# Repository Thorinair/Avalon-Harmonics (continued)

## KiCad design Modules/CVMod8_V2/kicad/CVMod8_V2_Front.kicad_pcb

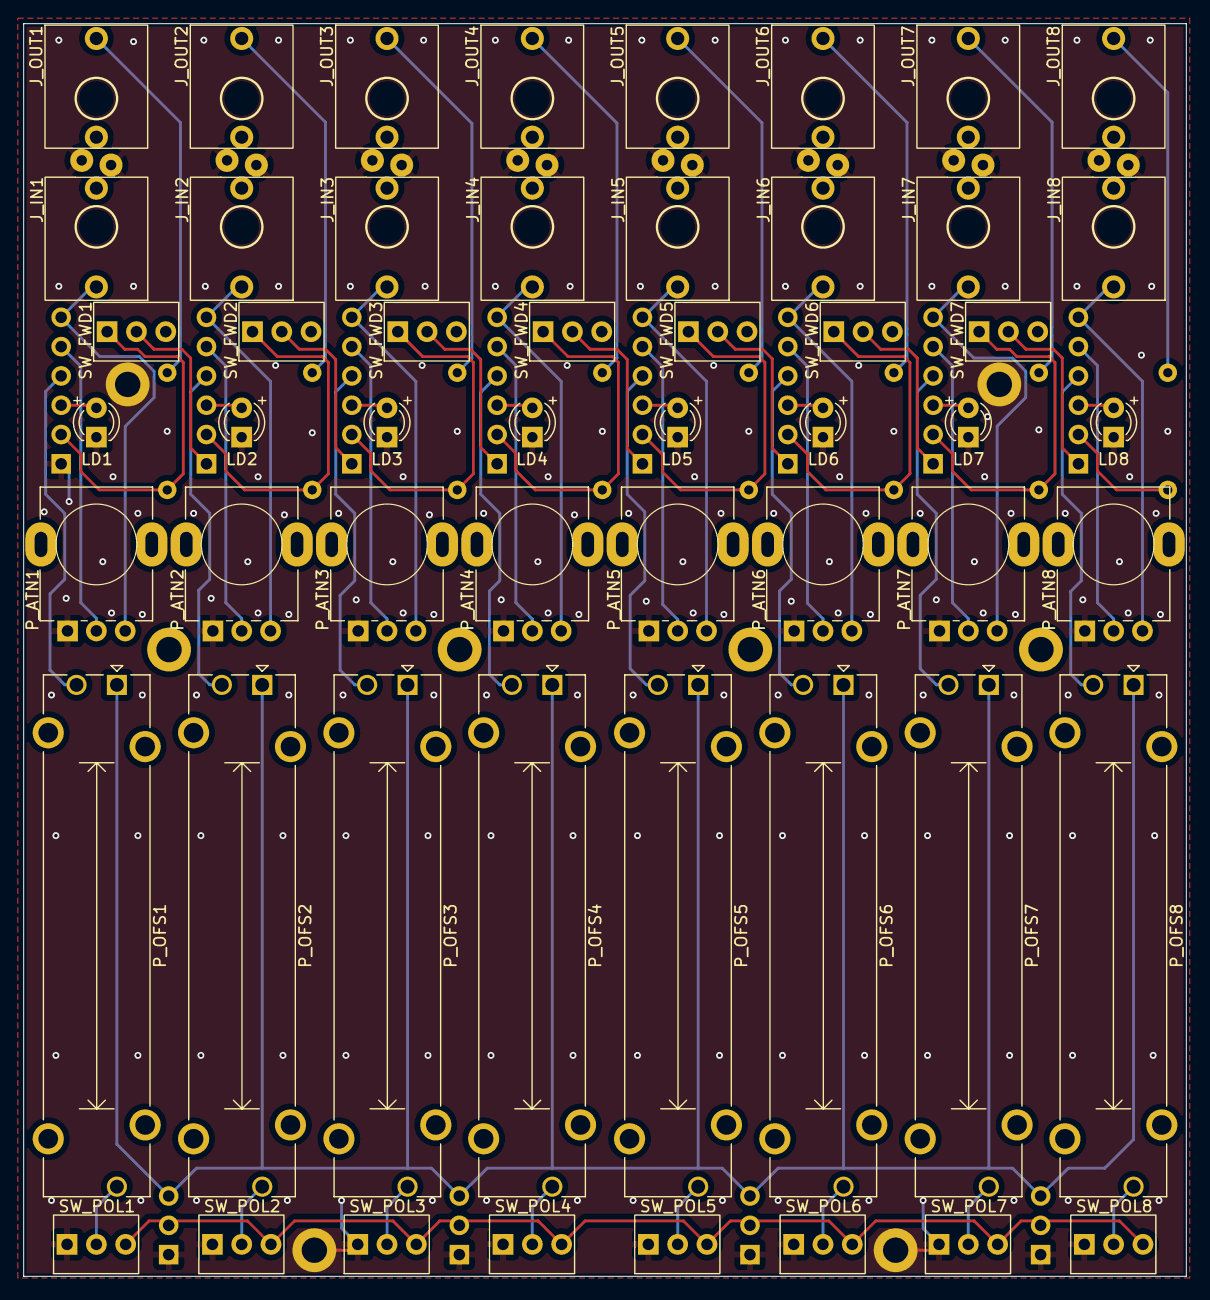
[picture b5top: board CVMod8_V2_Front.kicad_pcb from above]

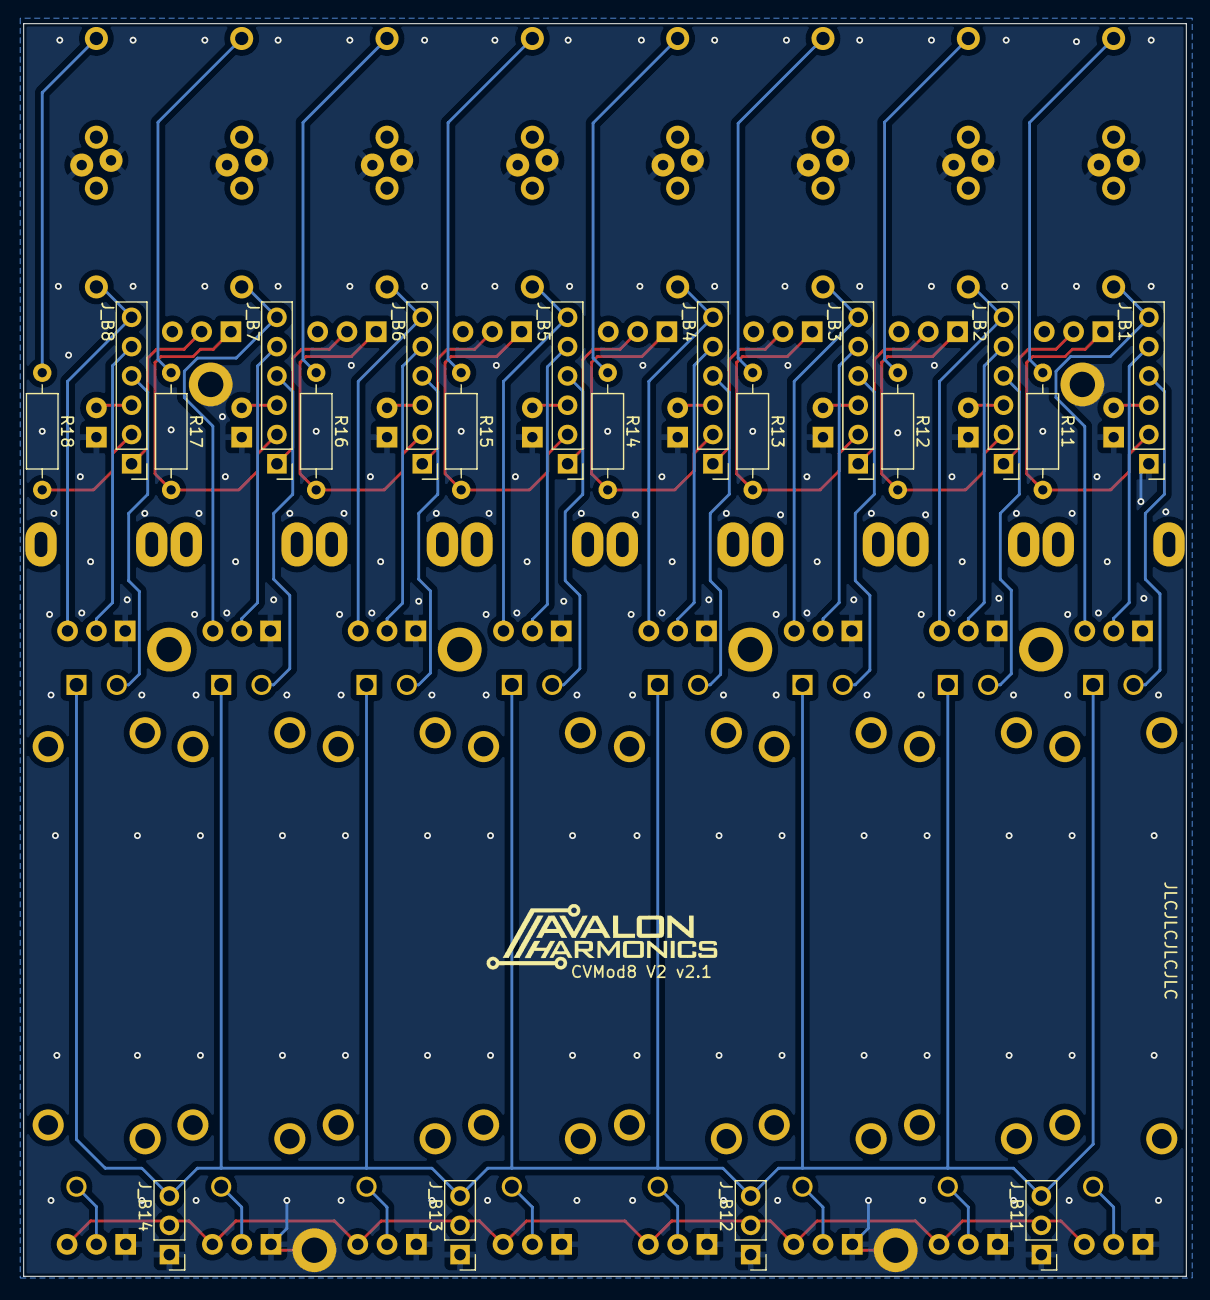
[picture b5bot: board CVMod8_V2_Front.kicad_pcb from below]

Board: 2 copper layers, 100.8 x 108.6 mm, 75 parts (20 on the bottom side), 66 nets.

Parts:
J_B1, J_B2, J_B3, J_B4, J_B5, J_B6, J_B7, J_B8: Conn_01x06_Female; PinHeader_1x06_P2.54mm_Vertical
J_B11, J_B12, J_B13, J_B14: Conn_01x03_Female; PinHeader_1x03_P2.54mm_Vertical
J_IN1, J_IN2, J_IN3, J_IN4, J_IN5, J_IN6, J_IN7, J_IN8: PJ301M-12; PJ301M-12 Offset
J_OUT1, J_OUT2, J_OUT3, J_OUT4, J_OUT5, J_OUT6, J_OUT7, J_OUT8: PJ301M-12; PJ301M-12 Offset
LD1, LD2, LD3, LD4, LD5, LD6, LD7, LD8: LED (Bi); LED_D3.0mm_FlatTop
P_ATN1, P_ATN2, P_ATN3, P_ATN4, P_ATN5, P_ATN6, P_ATN7, P_ATN8: B100k; Potentiometer Song Huei 9mm Trimmer
P_OFS1, P_OFS2, P_OFS3, P_OFS4, P_OFS5, P_OFS6, P_OFS7, P_OFS8: B100k; Potentiometer_Bourns_PTA3043_Single_Slide
R11, R12, R13, R14, R15, R16, R17, R18: 1k; R_Axial_DIN0207_L6.3mm_D2.5mm_P10.16mm_Horizontal
SW_FWD1, SW_FWD2, SW_FWD3, SW_FWD4, SW_FWD5, SW_FWD6, SW_FWD7: SW_SPDT; SPDT
SW_POL1, SW_POL2, SW_POL3, SW_POL4, SW_POL5, SW_POL6, SW_POL7, SW_POL8: SW_SPDT; SPDT

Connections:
+5V: J_B11.3, J_B12.3, J_B13.3, J_B14.3, P_OFS1.1, P_OFS2.1, P_OFS3.1, P_OFS4.1, P_OFS5.1, P_OFS6.1, P_OFS7.1, P_OFS8.1
-5V: J_B11.2, J_B12.2, J_B13.2, J_B14.2, SW_POL1.3 (C), SW_POL2.3 (C), SW_POL3.3 (C), SW_POL4.3 (C), SW_POL5.3 (C), SW_POL6.3 (C), SW_POL7.3 (C), SW_POL8.3 (C)
/FWD1: J_B2.1, SW_FWD1.2 (B)
/FWD2: J_B3.1, SW_FWD2.2 (B)
/FWD3: J_B4.1, SW_FWD3.2 (B)
/FWD4: J_B5.1, SW_FWD4.2 (B)
/FWD5: J_B6.1, SW_FWD5.2 (B)
/FWD6: J_B7.1, SW_FWD6.2 (B)
/FWD7: J_B8.1, SW_FWD7.2 (B)
GND: J_B1.1, J_B11.1, J_B12.1, J_B13.1, J_B14.1, J_IN1.GND, J_IN2.GND, J_IN3.GND, J_IN4.GND, J_IN5.GND, J_IN6.GND, J_IN7.GND, J_IN8.GND, J_OUT1.GND, J_OUT2.GND, J_OUT3.GND, J_OUT4.GND, J_OUT5.GND, J_OUT6.GND, J_OUT7.GND, J_OUT8.GND, LD1.1 (K), LD2.1 (K), LD3.1 (K), LD4.1 (K), LD5.1 (K), LD6.1 (K), LD7.1 (K), LD8.1 (K), P_ATN1.1, P_ATN2.1, P_ATN3.1, P_ATN4.1, P_ATN5.1, P_ATN6.1, P_ATN7.1, P_ATN8.1, SW_POL1.1 (A), SW_POL2.1 (A), SW_POL3.1 (A), SW_POL4.1 (A), SW_POL5.1 (A), SW_POL6.1 (A), SW_POL7.1 (A), SW_POL8.1 (A)
unnamed: J_B1.2, R11.1, SW_FWD1.1 (A)
unnamed: J_B1.3, LD1.2 (A)
unnamed: J_B1.4, P_OFS1.2
unnamed: J_B1.5, P_ATN1.2
unnamed: J_B1.6, J_IN1.SIG, P_ATN1.3
unnamed: J_B2.2, R12.1, SW_FWD2.1 (A)
unnamed: J_B2.3, LD2.2 (A)
unnamed: J_B2.4, P_OFS2.2
unnamed: J_B2.5, P_ATN2.2
unnamed: J_B2.6, J_IN2.SIG, P_ATN2.3
unnamed: J_B3.2, R13.1, SW_FWD3.1 (A)
unnamed: J_B3.3, LD3.2 (A)
unnamed: J_B3.4, P_OFS3.2
unnamed: J_B3.5, P_ATN3.2
unnamed: J_B3.6, J_IN3.SIG, P_ATN3.3
unnamed: J_B4.2, R14.1, SW_FWD4.1 (A)
unnamed: J_B4.3, LD4.2 (A)
unnamed: J_B4.4, P_OFS4.2
unnamed: J_B4.5, P_ATN4.2
unnamed: J_B4.6, J_IN4.SIG, P_ATN4.3
unnamed: J_B5.2, R15.1, SW_FWD5.1 (A)
unnamed: J_B5.3, LD5.2 (A)
unnamed: J_B5.4, P_OFS5.2
unnamed: J_B5.5, P_ATN5.2
unnamed: J_B5.6, J_IN5.SIG, P_ATN5.3
unnamed: J_B6.2, R16.1, SW_FWD6.1 (A)
unnamed: J_B6.3, LD6.2 (A)
unnamed: J_B6.4, P_OFS6.2
unnamed: J_B6.5, P_ATN6.2
unnamed: J_B6.6, J_IN6.SIG, P_ATN6.3
unnamed: J_B7.2, R17.1, SW_FWD7.1 (A)
unnamed: J_B7.3, LD7.2 (A)
unnamed: J_B7.4, P_OFS7.2
unnamed: J_B7.5, P_ATN7.2
unnamed: J_B7.6, J_IN7.SIG, P_ATN7.3
unnamed: J_B8.2, R18.1
unnamed: J_B8.3, LD8.2 (A)
unnamed: J_B8.4, P_OFS8.2
unnamed: J_B8.5, P_ATN8.2
unnamed: J_B8.6, J_IN8.SIG, P_ATN8.3
unnamed: J_OUT1.SIG, R11.2
unnamed: J_OUT2.SIG, R12.2
unnamed: J_OUT3.SIG, R13.2
unnamed: J_OUT4.SIG, R14.2
unnamed: J_OUT5.SIG, R15.2
unnamed: J_OUT6.SIG, R16.2
unnamed: J_OUT7.SIG, R17.2
unnamed: J_OUT8.SIG, R18.2
unnamed: P_OFS1.3, SW_POL1.2 (B)
unnamed: P_OFS2.3, SW_POL2.2 (B)
unnamed: P_OFS3.3, SW_POL3.2 (B)
unnamed: P_OFS4.3, SW_POL4.2 (B)
unnamed: P_OFS5.3, SW_POL5.2 (B)
unnamed: P_OFS6.3, SW_POL6.2 (B)
unnamed: P_OFS7.3, SW_POL7.2 (B)
unnamed: P_OFS8.3, SW_POL8.2 (B)
